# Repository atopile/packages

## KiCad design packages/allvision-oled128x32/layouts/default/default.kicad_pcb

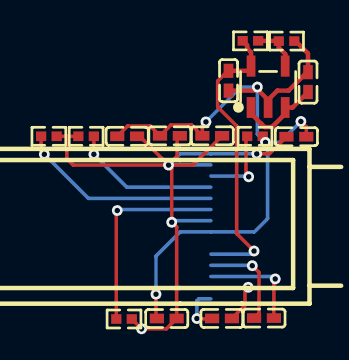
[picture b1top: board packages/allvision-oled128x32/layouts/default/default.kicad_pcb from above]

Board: 2 copper layers, 17 parts (0 on the bottom side), 14 nets.

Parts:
C1, C2, C3, C4: 1µF ±10% 25V X5R; C0402
C5, C8: 100nF ±10% 16V X7R; C0402
C6, C9: 4.7µF ±20% 10V X5R; C0402
C7: 2.2µF ±20% 6.3V X5R; C0402
OLED1: OLED-SMD_N087-2832TSWYG02-H14_1
R1: 510kΩ ±1% 62.5mW; R0402
R2, R3, R4, R5, R6: 10kΩ ±1% 62.5mW; R0402
U1: SOT-23-5_L3.0-W1.7-P0.95-LS2.8-BL

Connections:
C1N: C1.1, OLED1.4
C1P: C1.2, OLED1.3
C2N: C2.1, OLED1.2
C2P: C2.2, OLED1.1
IREF: OLED1.12, R1.1
SCL: OLED1.10, R5.1
SDA: OLED1.11, R6.1
VDIV_OUTPUT: R2.1, R3.2, U1.4
nRES: OLED1.9, R4.1
power_in-VCC: C3.1, U1.1, U1.3
power_out-GND: C3.2, C4.2, R2.2, U1.2
power_out-VCC: C4.1, OLED1.5, R3.1, U1.5
power_shim-GND: C5.2, C6.2, C7.2, C8.2, C9.2, OLED1.7, R1.2
power_shim-VCC: C5.1, C6.1, C7.1, C8.1, C9.1, OLED1.8, OLED1.13, OLED1.14, R4.2, R5.2, R6.2

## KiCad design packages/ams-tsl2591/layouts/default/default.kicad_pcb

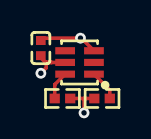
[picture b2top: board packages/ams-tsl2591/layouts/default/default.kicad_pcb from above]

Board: 2 copper layers, 4 parts (0 on the bottom side), 4 nets.

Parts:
C1: {8.999..1.1}F; C0402
R1, R2: 10000±1.0%Ω; R0402
U1: DFN-6_L2.4-W2.0-P0.65-BL

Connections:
SCL: R1.1, U1.1
SDA: R2.1, U1.6
hv: C1.1, R1.2, R2.2, U1.5
lv: C1.2, U1.3
